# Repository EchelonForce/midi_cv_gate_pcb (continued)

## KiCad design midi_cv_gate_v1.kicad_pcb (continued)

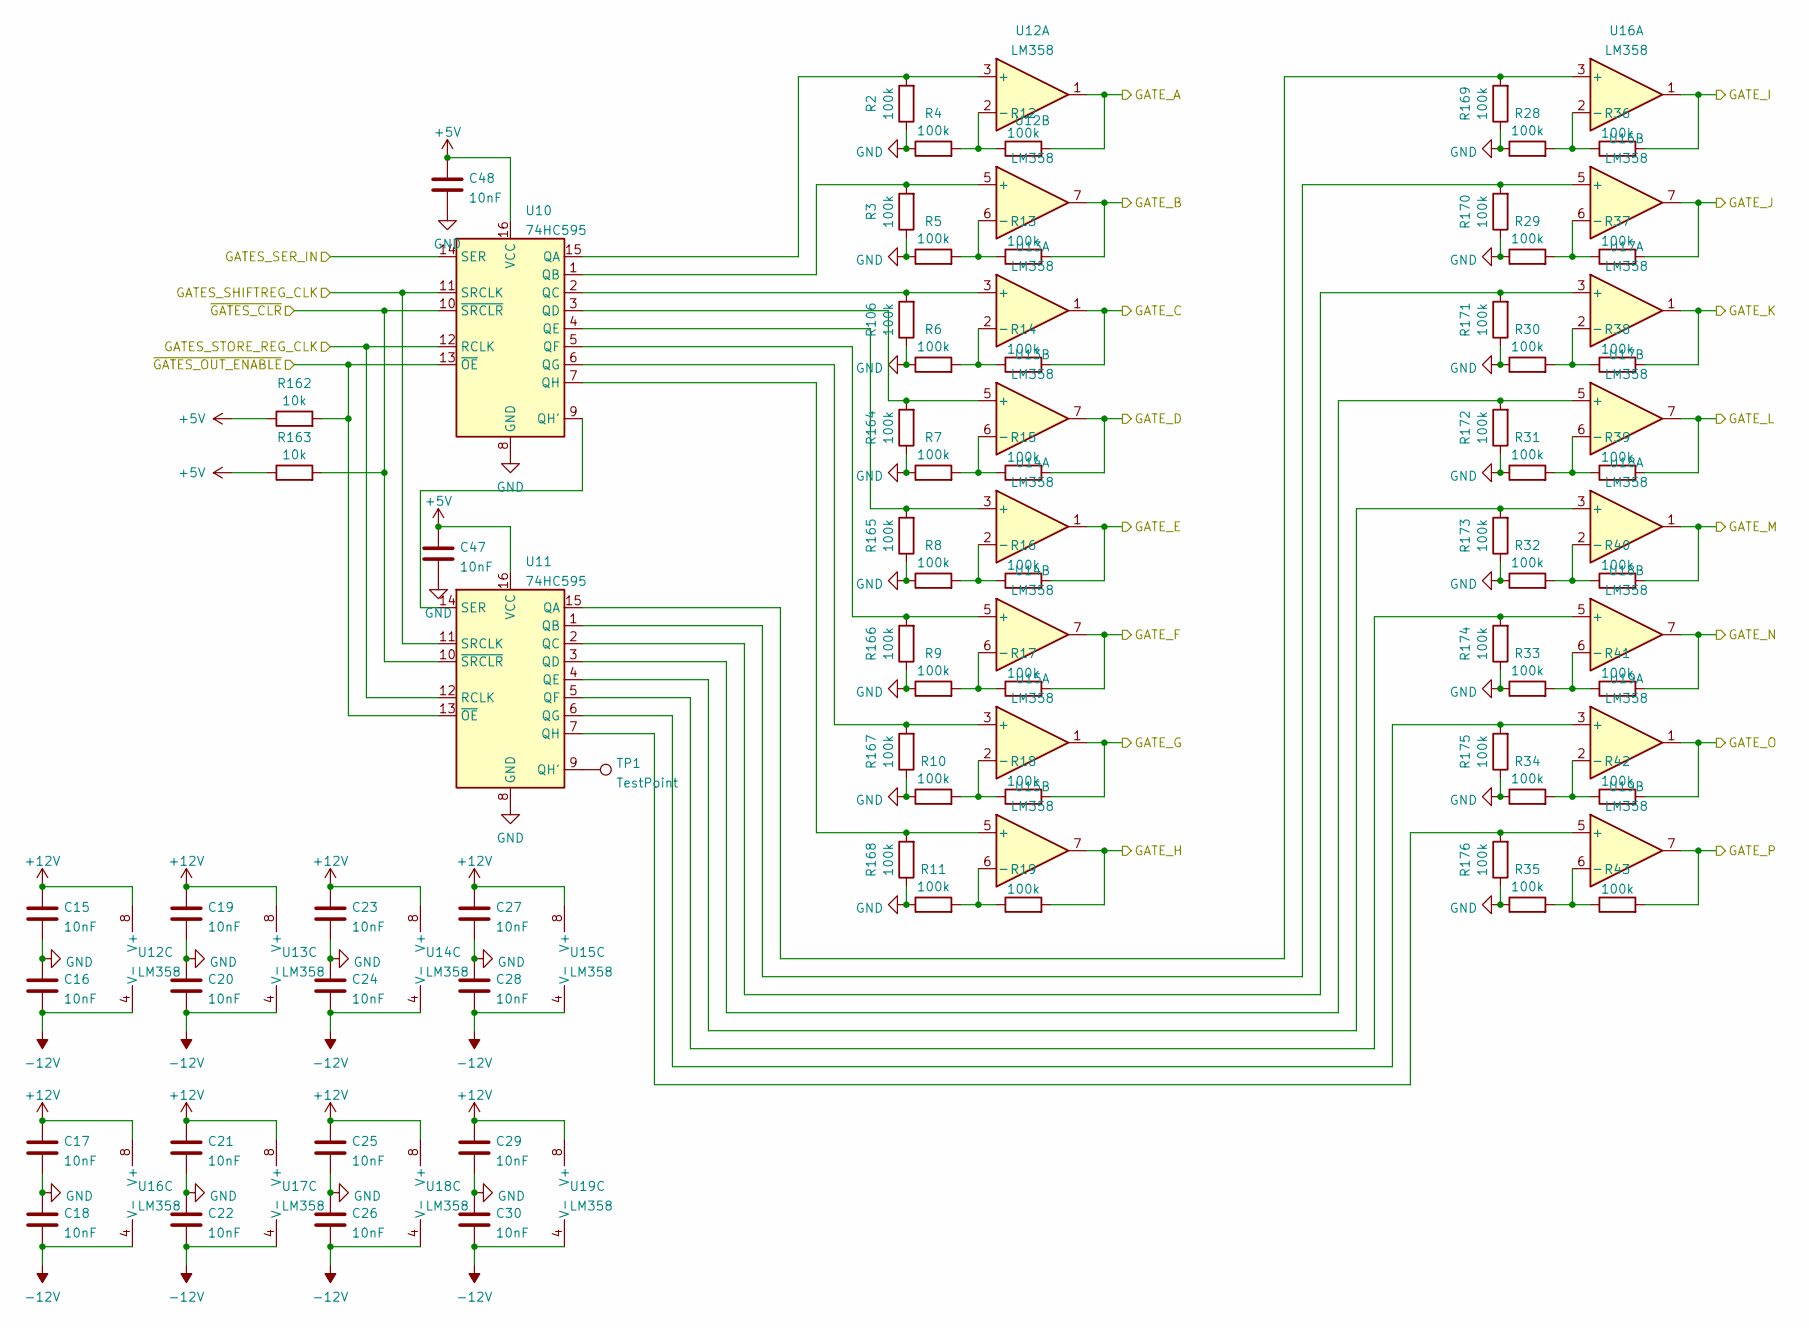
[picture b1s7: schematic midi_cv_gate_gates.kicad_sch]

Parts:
C15, C16, C17, C18, C19, C20, C21, C22, C23, C24, C25, C26, C27, C28, C29, C30, C47, C48: 10nF; C_1206_3216Metric_Pad1.33x1.80mm_HandSolder
R2, R3, R4, R5, R6, R7, R8, R9, R10, R11, R12, R13, R14, R15, R16, R17, R18, R19, R28, R29, R30, R31, R32, R33, R34, R35, R36, R37, R38, R39, R40, R41, R42, R43, R106, R164, R165, R166, R167, R168, R169, R170, R171, R172, R173, R174, R175, R176: 100k; R_1206_3216Metric_Pad1.30x1.75mm_HandSolder
R162, R163: 10k; R_1206_3216Metric_Pad1.30x1.75mm_HandSolder
TP1: TestPoint; TestPoint_Pad_D1.0mm
U10, U11: 74HC595; SOIC-16_3.9x9.9mm_P1.27mm
U12, U13, U14, U15, U16, U17, U18, U19: LM358; DIP-8_W7.62mm_Socket_LongPads

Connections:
+5V: C47.1, C48.1, R162.1, R163.1, U10.16 (VCC), U11.16 (VCC); also elsewhere on the board
+12V: C15.1, C17.1, C19.1, C21.1, C23.1, C25.1, C27.1, C29.1, U12.8 (V+), U13.8 (V+), U14.8 (V+), U15.8 (V+), U16.8 (V+), U17.8 (V+), U18.8 (V+), U19.8 (V+); also elsewhere on the board
-12V: C16.2, C18.2, C20.2, C22.2, C24.2, C26.2, C28.2, C30.2, U12.4 (V-), U13.4 (V-), U14.4 (V-), U15.4 (V-), U16.4 (V-), U17.4 (V-), U18.4 (V-), U19.4 (V-); also elsewhere on the board
/CONTROLLER/CNTRL_GATES_SHIFTREG_CLK: U10.11 (SRCLK), U11.11 (SRCLK); also elsewhere on the board
/CONTROLLER/CNTRL_GATES_STORE_REG_CLK: U10.12 (RCLK), U11.12 (RCLK); also elsewhere on the board
/CONTROLLER/CNTRL_GATE_SER_IN: U10.14 (SER); also elsewhere on the board
/CONTROLLER/~CNTRL_GATES_CLR: R163.2, U10.10 (~SRCLR), U11.10 (~SRCLR); also elsewhere on the board
/CONTROLLER/~CNTRL_GATES_OUT_ENABLE: R162.2, U10.13 (~OE), U11.13 (~OE); also elsewhere on the board
/GATES/GATE_A: R12.2, U12.1; also elsewhere on the board
/GATES/GATE_B: R13.2, U12.7; also elsewhere on the board
/GATES/GATE_C: R14.2, U13.1; also elsewhere on the board
/GATES/GATE_D: R15.2, U13.7; also elsewhere on the board
/GATES/GATE_E: R16.2, U14.1; also elsewhere on the board
/GATES/GATE_F: R17.2, U14.7; also elsewhere on the board
/GATES/GATE_G: R18.2, U15.1; also elsewhere on the board
/GATES/GATE_H: R19.2, U15.7; also elsewhere on the board
/GATES/GATE_I: R36.2, U16.1; also elsewhere on the board
/GATES/GATE_J: R37.2, U16.7; also elsewhere on the board
/GATES/GATE_K: R38.2, U17.1; also elsewhere on the board
/GATES/GATE_L: R39.2, U17.7; also elsewhere on the board
/GATES/GATE_M: R40.2, U18.1; also elsewhere on the board
/GATES/GATE_N: R41.2, U18.7; also elsewhere on the board
/GATES/GATE_O: R42.2, U19.1; also elsewhere on the board
/GATES/GATE_P: R43.2, U19.7; also elsewhere on the board
GND: C15.2, C16.1, C17.2, C18.1, C19.2, C20.1, C21.2, C22.1, C23.2, C24.1, C25.2, C26.1, C27.2, C28.1, C29.2, C30.1, C47.2, C48.2, R2.1, R3.1, R4.1, R5.1, R6.1, R7.1, R8.1, R9.1, R10.1, R11.1, R28.1, R29.1, R30.1, R31.1, R32.1, R33.1, R34.1, R35.1, R106.1, R164.1, R165.1, R166.1, R167.1, R168.1, R169.1, R170.1, R171.1, R172.1, R173.1, R174.1, R175.1, R176.1, U10.8 (GND), U11.8 (GND); also elsewhere on the board
unnamed: R2.2, U10.15 (QA), U12.3 (+)
unnamed: R3.2, U10.1 (QB), U12.5 (+)
unnamed: R10.2, R18.1, U15.2 (-)
unnamed: R11.2, R19.1, U15.6 (-)
unnamed: R4.2, R12.1, U12.2 (-)
unnamed: R5.2, R13.1, U12.6 (-)
unnamed: R6.2, R14.1, U13.2 (-)
unnamed: R7.2, R15.1, U13.6 (-)
unnamed: R8.2, R16.1, U14.2 (-)
unnamed: R9.2, R17.1, U14.6 (-)
unnamed: R28.2, R36.1, U16.2 (-)
unnamed: R29.2, R37.1, U16.6 (-)
unnamed: R30.2, R38.1, U17.2 (-)
unnamed: R31.2, R39.1, U17.6 (-)
unnamed: R32.2, R40.1, U18.2 (-)
unnamed: R33.2, R41.1, U18.6 (-)
unnamed: R34.2, R42.1, U19.2 (-)
unnamed: R35.2, R43.1, U19.6 (-)
unnamed: R106.2, U10.2 (QC), U13.3 (+)
unnamed: R164.2, U10.3 (QD), U13.5 (+)
unnamed: R165.2, U10.4 (QE), U14.3 (+)
unnamed: R166.2, U10.5 (QF), U14.5 (+)
unnamed: R167.2, U10.6 (QG), U15.3 (+)
unnamed: R168.2, U10.7 (QH), U15.5 (+)
unnamed: R169.2, U11.15 (QA), U16.3 (+)
unnamed: R170.2, U11.1 (QB), U16.5 (+)
unnamed: R171.2, U11.2 (QC), U17.3 (+)
unnamed: R172.2, U11.3 (QD), U17.5 (+)
unnamed: R173.2, U11.4 (QE), U18.3 (+)
unnamed: R174.2, U11.5 (QF), U18.5 (+)
unnamed: R175.2, U11.6 (QG), U19.3 (+)
unnamed: R176.2, U11.7 (QH), U19.5 (+)
unnamed: TP1.1, U11.9 (QH')
unnamed: U10.9 (QH'), U11.14 (SER)

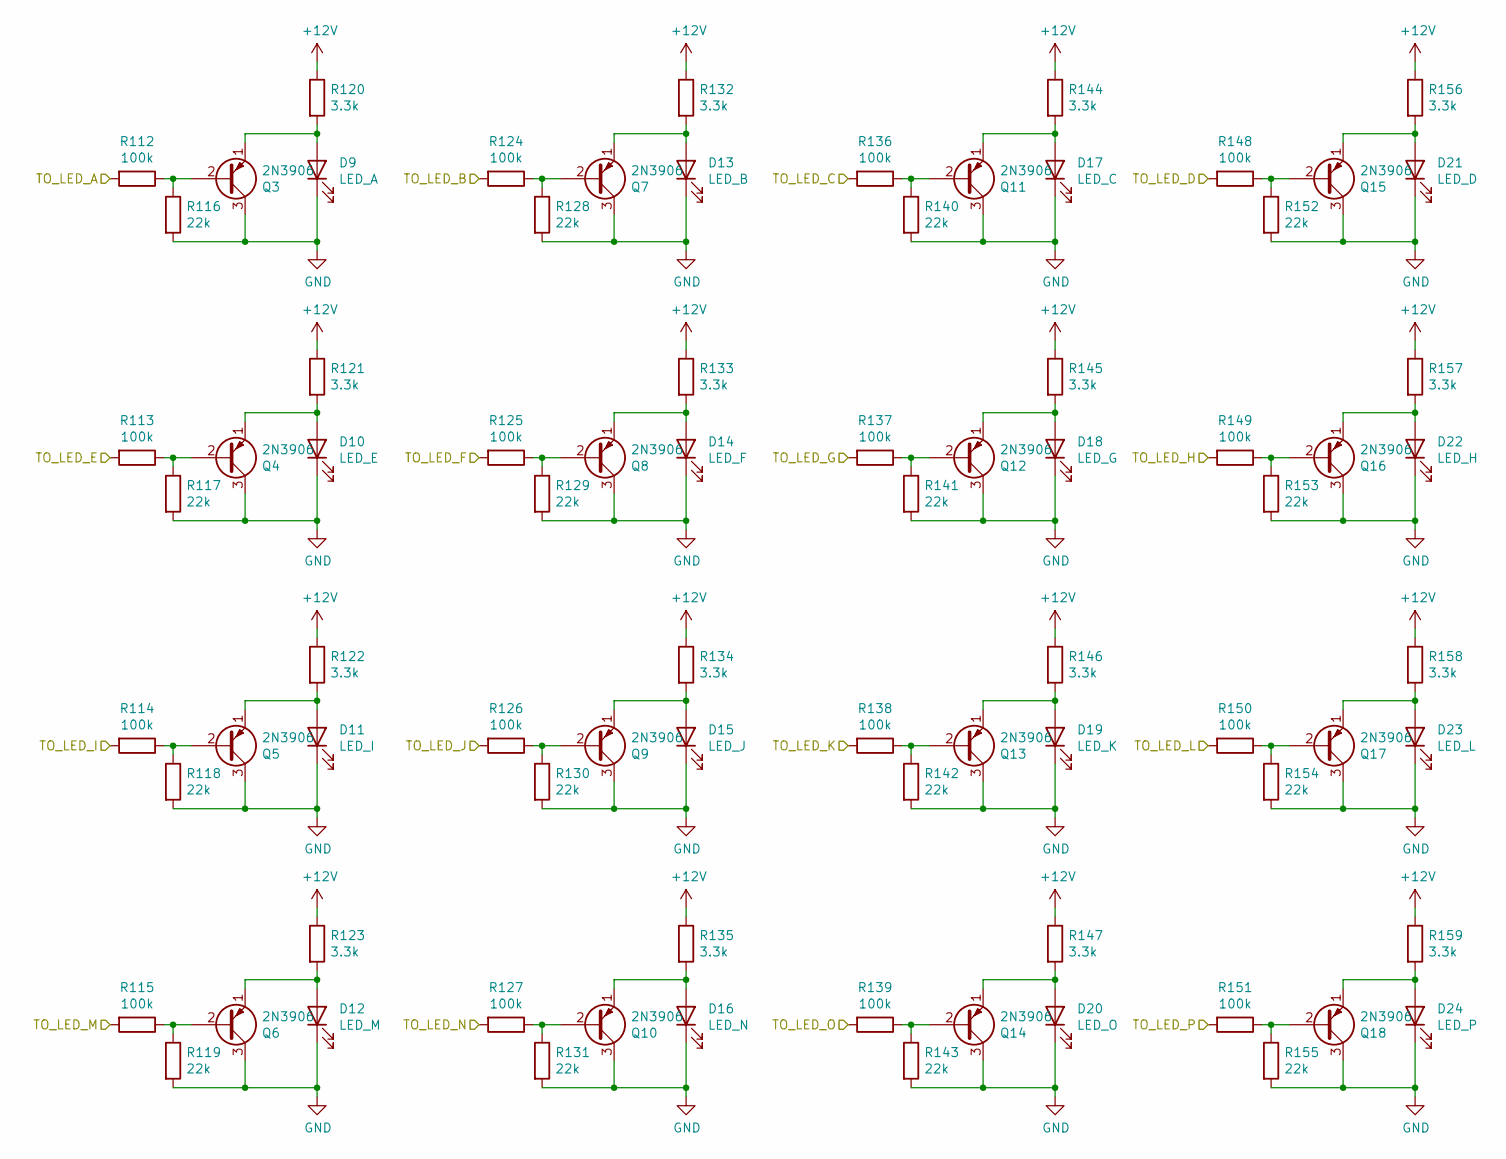
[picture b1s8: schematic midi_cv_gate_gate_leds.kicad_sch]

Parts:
D9: LED_A; LED_D3.0mm
D10: LED_E; LED_D3.0mm
D11: LED_I; LED_D3.0mm
D12: LED_M; LED_D3.0mm
D13: LED_B; LED_D3.0mm
D14: LED_F; LED_D3.0mm
D15: LED_J; LED_D3.0mm
D16: LED_N; LED_D3.0mm
D17: LED_C; LED_D3.0mm
D18: LED_G; LED_D3.0mm
D19: LED_K; LED_D3.0mm
D20: LED_O; LED_D3.0mm
D21: LED_D; LED_D3.0mm
D22: LED_H; LED_D3.0mm
D23: LED_L; LED_D3.0mm
D24: LED_P; LED_D3.0mm
Q3, Q4, Q5, Q6, Q7, Q8, Q9, Q10, Q11, Q12, Q13, Q14, Q15, Q16, Q17, Q18: 2N3906; TO-92_Inline_Wide
R112, R113, R114, R115, R124, R125, R126, R127, R136, R137, R138, R139, R148, R149, R150, R151: 100k; R_1206_3216Metric_Pad1.30x1.75mm_HandSolder
R116, R117, R118, R119, R128, R129, R130, R131, R140, R141, R142, R143, R152, R153, R154, R155: 22k; R_1206_3216Metric_Pad1.30x1.75mm_HandSolder
R120, R121, R122, R123, R132, R133, R134, R135, R144, R145, R146, R147, R156, R157, R158, R159: 3.3k; R_1206_3216Metric_Pad1.30x1.75mm_HandSolder

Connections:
+12V: R120.1, R121.1, R122.1, R123.1, R132.1, R133.1, R134.1, R135.1, R144.1, R145.1, R146.1, R147.1, R156.1, R157.1, R158.1, R159.1; also elsewhere on the board
/GATE_LEDs/TO_LED_A: R112.2; also elsewhere on the board
/GATE_LEDs/TO_LED_B: R124.2; also elsewhere on the board
/GATE_LEDs/TO_LED_C: R136.2; also elsewhere on the board
/GATE_LEDs/TO_LED_D: R148.2; also elsewhere on the board
/GATE_LEDs/TO_LED_E: R113.2; also elsewhere on the board
/GATE_LEDs/TO_LED_F: R125.2; also elsewhere on the board
/GATE_LEDs/TO_LED_G: R137.2; also elsewhere on the board
/GATE_LEDs/TO_LED_H: R149.2; also elsewhere on the board
/GATE_LEDs/TO_LED_I: R114.2; also elsewhere on the board
/GATE_LEDs/TO_LED_J: R126.2; also elsewhere on the board
/GATE_LEDs/TO_LED_K: R138.2; also elsewhere on the board
/GATE_LEDs/TO_LED_L: R150.2; also elsewhere on the board
/GATE_LEDs/TO_LED_M: R115.2; also elsewhere on the board
/GATE_LEDs/TO_LED_N: R127.2; also elsewhere on the board
/GATE_LEDs/TO_LED_O: R139.2; also elsewhere on the board
/GATE_LEDs/TO_LED_P: R151.2; also elsewhere on the board
GND: D9.1 (K), D10.1 (K), D11.1 (K), D12.1 (K), D13.1 (K), D14.1 (K), D15.1 (K), D16.1 (K), D17.1 (K), D18.1 (K), D19.1 (K), D20.1 (K), D21.1 (K), D22.1 (K), D23.1 (K), D24.1 (K), Q3.3 (C), Q4.3 (C), Q5.3 (C), Q6.3 (C), Q7.3 (C), Q8.3 (C), Q9.3 (C), Q10.3 (C), Q11.3 (C), Q12.3 (C), Q13.3 (C), Q14.3 (C), Q15.3 (C), Q16.3 (C), Q17.3 (C), Q18.3 (C), R116.2, R117.2, R118.2, R119.2, R128.2, R129.2, R130.2, R131.2, R140.2, R141.2, R142.2, R143.2, R152.2, R153.2, R154.2, R155.2; also elsewhere on the board
unnamed: D9.2 (A), Q3.1 (E), R120.2
unnamed: D10.2 (A), Q4.1 (E), R121.2
unnamed: D11.2 (A), Q5.1 (E), R122.2
unnamed: D12.2 (A), Q6.1 (E), R123.2
unnamed: D13.2 (A), Q7.1 (E), R132.2
unnamed: D14.2 (A), Q8.1 (E), R133.2
unnamed: D15.2 (A), Q9.1 (E), R134.2
unnamed: D16.2 (A), Q10.1 (E), R135.2
unnamed: D17.2 (A), Q11.1 (E), R144.2
unnamed: D18.2 (A), Q12.1 (E), R145.2
unnamed: D19.2 (A), Q13.1 (E), R146.2
unnamed: D20.2 (A), Q14.1 (E), R147.2
unnamed: D21.2 (A), Q15.1 (E), R156.2
unnamed: D22.2 (A), Q16.1 (E), R157.2
unnamed: D23.2 (A), Q17.1 (E), R158.2
unnamed: D24.2 (A), Q18.1 (E), R159.2
unnamed: Q3.2 (B), R112.1, R116.1
unnamed: Q4.2 (B), R113.1, R117.1
unnamed: Q5.2 (B), R114.1, R118.1
unnamed: Q6.2 (B), R115.1, R119.1
unnamed: Q7.2 (B), R124.1, R128.1
unnamed: Q8.2 (B), R125.1, R129.1
unnamed: Q9.2 (B), R126.1, R130.1
unnamed: Q10.2 (B), R127.1, R131.1
unnamed: Q11.2 (B), R136.1, R140.1
unnamed: Q12.2 (B), R137.1, R141.1
unnamed: Q13.2 (B), R138.1, R142.1
unnamed: Q14.2 (B), R139.1, R143.1
unnamed: Q15.2 (B), R148.1, R152.1
unnamed: Q16.2 (B), R149.1, R153.1
unnamed: Q17.2 (B), R150.1, R154.1
unnamed: Q18.2 (B), R151.1, R155.1

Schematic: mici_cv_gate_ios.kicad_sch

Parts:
D6: LED_1; LED_D3.0mm
D8: LED_2; LED_D3.0mm
Q1, Q2: 2N3906; TO-92_Inline_Wide
R100, R101, R104: 100k; R_1206_3216Metric_Pad1.30x1.75mm_HandSolder
R102, R103: 22k; R_1206_3216Metric_Pad1.30x1.75mm_HandSolder
R110, R111: 3.3k; R_1206_3216Metric_Pad1.30x1.75mm_HandSolder
SW1: SW_SPST; SW_PS1024ALRED

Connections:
+5V: SW1.2 (B); also elsewhere on the board
+12V: R110.1, R111.1; also elsewhere on the board
/IOs/FROM_SW_1: R104.1, SW1.1 (A); also elsewhere on the board
/IOs/TO_LED_1: R100.2; also elsewhere on the board
/IOs/TO_LED_2: R101.2; also elsewhere on the board
GND: D6.1 (K), D8.1 (K), Q1.3 (C), Q2.3 (C), R102.2, R103.2, R104.2; also elsewhere on the board
unnamed: D6.2 (A), Q1.1 (E), R110.2
unnamed: D8.2 (A), Q2.1 (E), R111.2
unnamed: Q1.2 (B), R100.1, R102.1
unnamed: Q2.2 (B), R101.1, R103.1

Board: 2 copper layers, 364 parts (131 on the bottom side), 239 nets, no tracks yet.

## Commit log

2022-05-08 Initial commit with .gitignore for kicad
2022-05-08 v0.1 schematic mostly complete layout started no routing
2022-05-08 Removed midi jumpers and rearranging for routing
2022-05-08 More rearranging for routing
2022-05-09 Replace soic-14 with dip 14 for DACs, add pulldowns on opamp inputs
2022-05-12 Partially routed
2022-05-12 More routing
2022-05-14 Routing of main board done
2022-05-14 First pass routing done, ERC passes, except interboard nets
2022-05-14 Fixed alignment of jacks and LEDs
2022-05-14 Cleanups and title blocks
2022-09-08 Add schematic pdf and readme
